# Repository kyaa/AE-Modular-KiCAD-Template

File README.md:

# AE-Modular-KiCAD-Template
This is a very basic KiCAD template for AE Modular modules. There are two basic projects in this repo.
- 'Panel', a simple frontpanel design.
- 'PCB', a simple pcb layout with the headers already included.

The projects are both for a 1u module, but templates for 2, 3, and 4u are included on the 'User.9' layer.
Cheers!

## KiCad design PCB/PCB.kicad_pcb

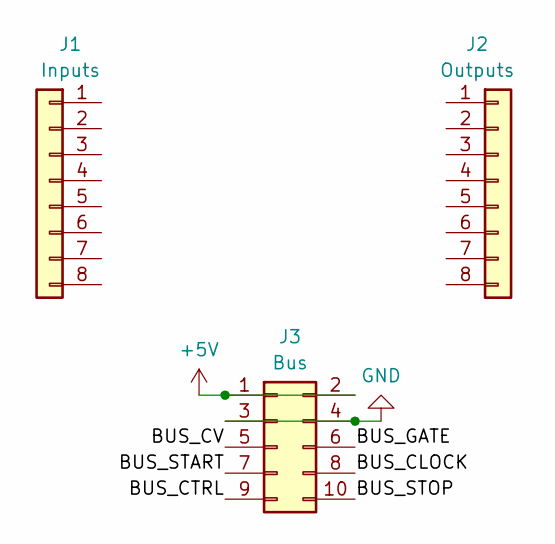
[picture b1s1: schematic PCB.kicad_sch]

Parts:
J1: Inputs; PinSocket_1x08_P2.54mm_Vertical
J2: Outputs; PinSocket_1x08_P2.54mm_Vertical
J3: Bus; PinSocket_2x05_P2.54mm_Vertical

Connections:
+5V: J3.1, J3.2
/BUS_CLOCK: J3.8
/BUS_CTRL: J3.9
/BUS_CV: J3.5
/BUS_GATE: J3.6
/BUS_START: J3.7
/BUS_STOP: J3.10
GND: J3.3, J3.4

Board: 2 copper layers, 3 parts (1 on the bottom side), 2 nets, no tracks yet.

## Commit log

2022-06-01 Initial commit.
